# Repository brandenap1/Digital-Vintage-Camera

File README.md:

# Digital-Vintage-Camera
Arduino-controlled image sensor array housed in an analog Conley Kewpie No. 2A analog camera

Mechanical Housing: 3D printed enclosure to house PCBs in camera
Image Sensor PCB: 16 x 16 phototransistor array with MUX control
Controller PCB: MCU with ADC for image data processing 

Future Versions: More optical sensors for higher resolution, Better ADC with RAM for instant image capture, and electronics to automatically move aperture dial

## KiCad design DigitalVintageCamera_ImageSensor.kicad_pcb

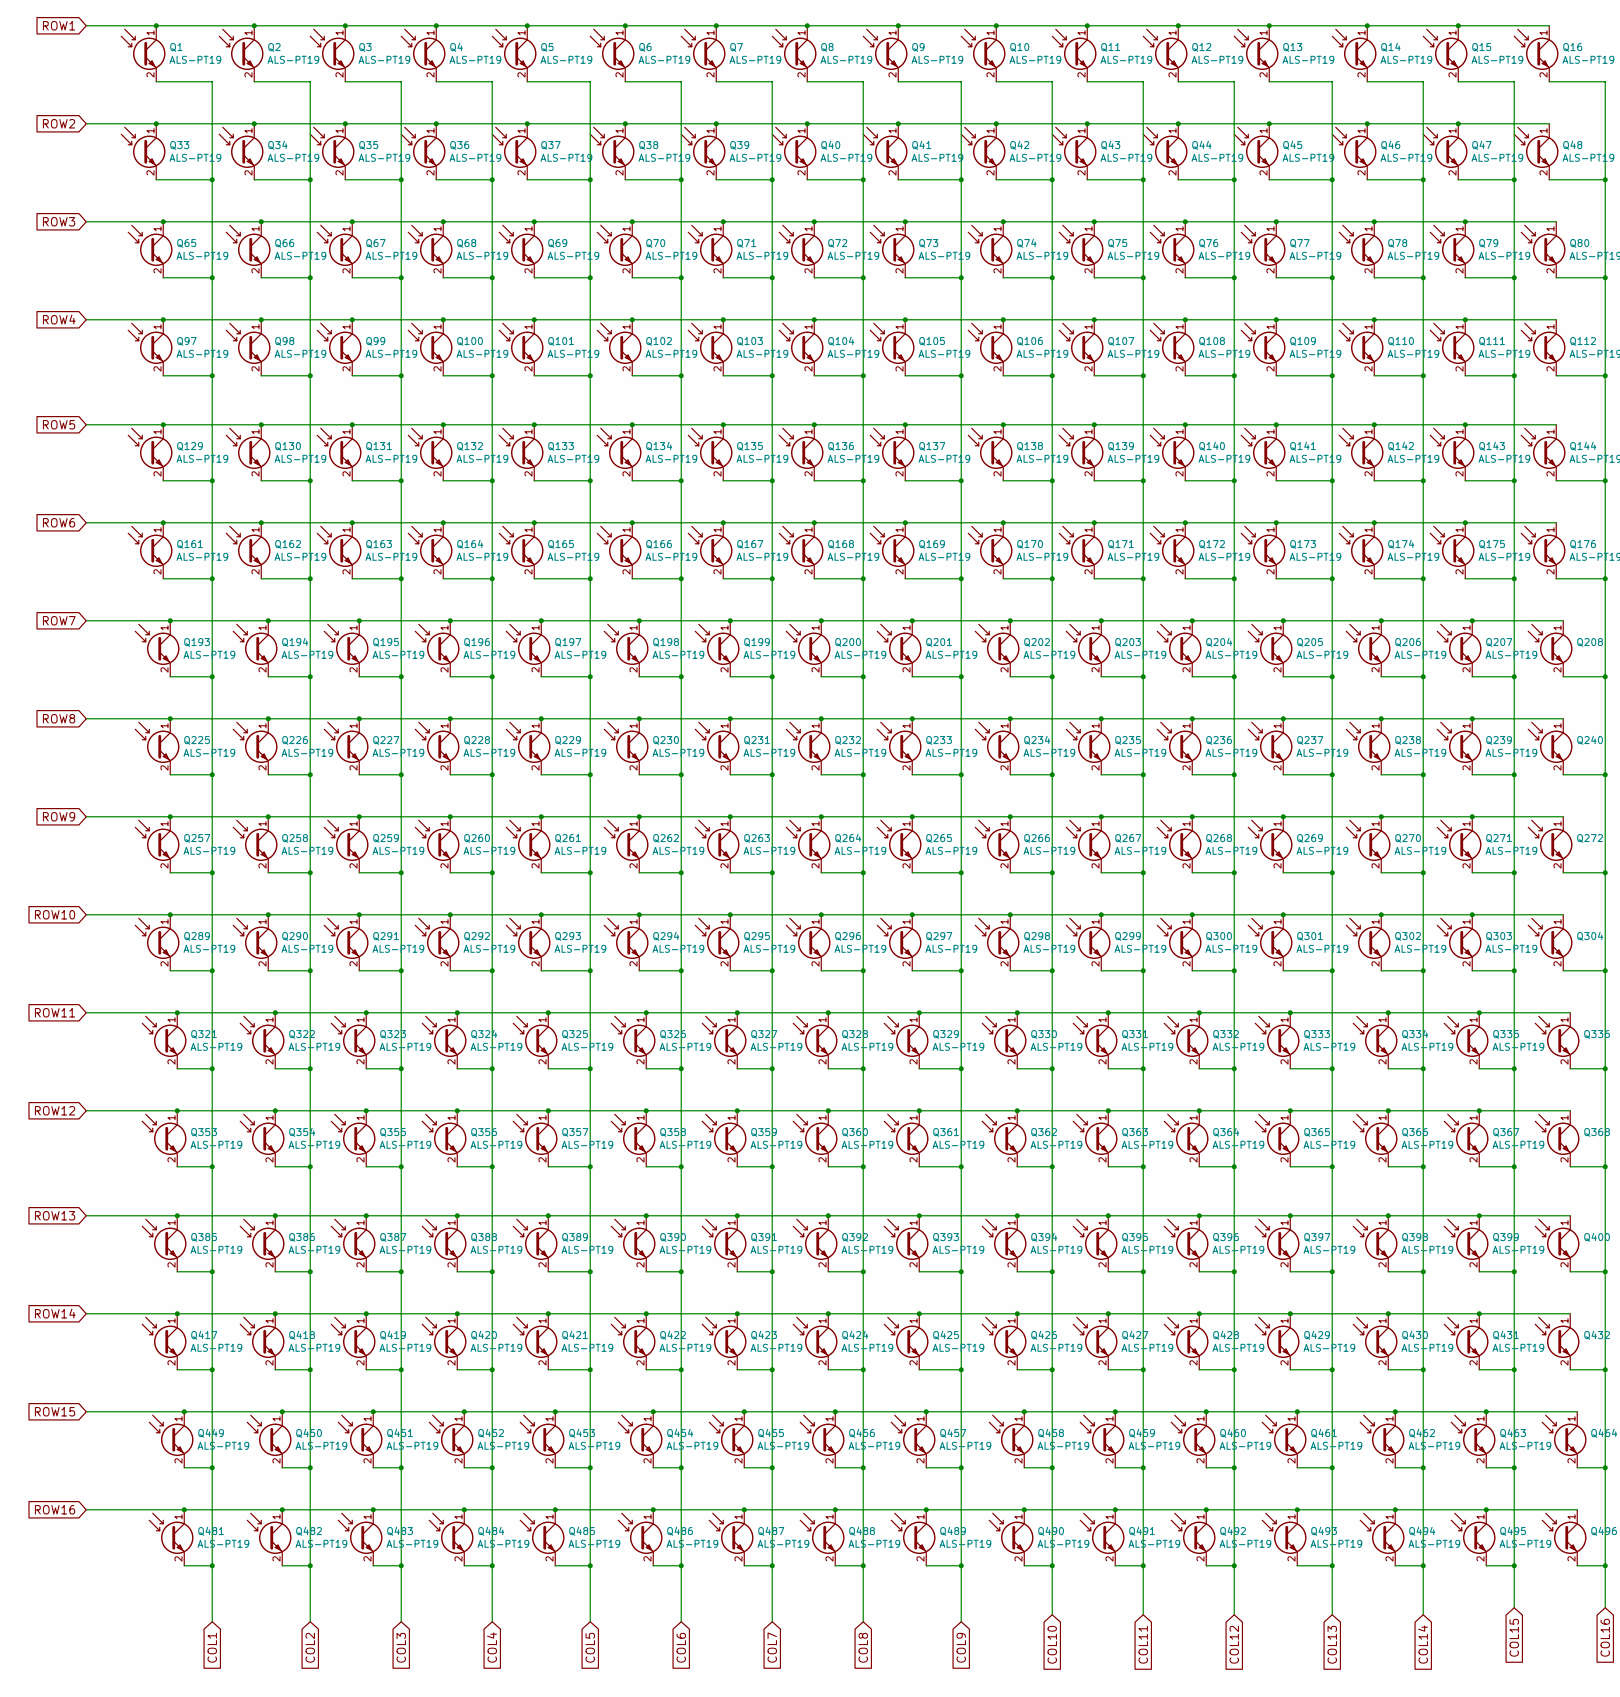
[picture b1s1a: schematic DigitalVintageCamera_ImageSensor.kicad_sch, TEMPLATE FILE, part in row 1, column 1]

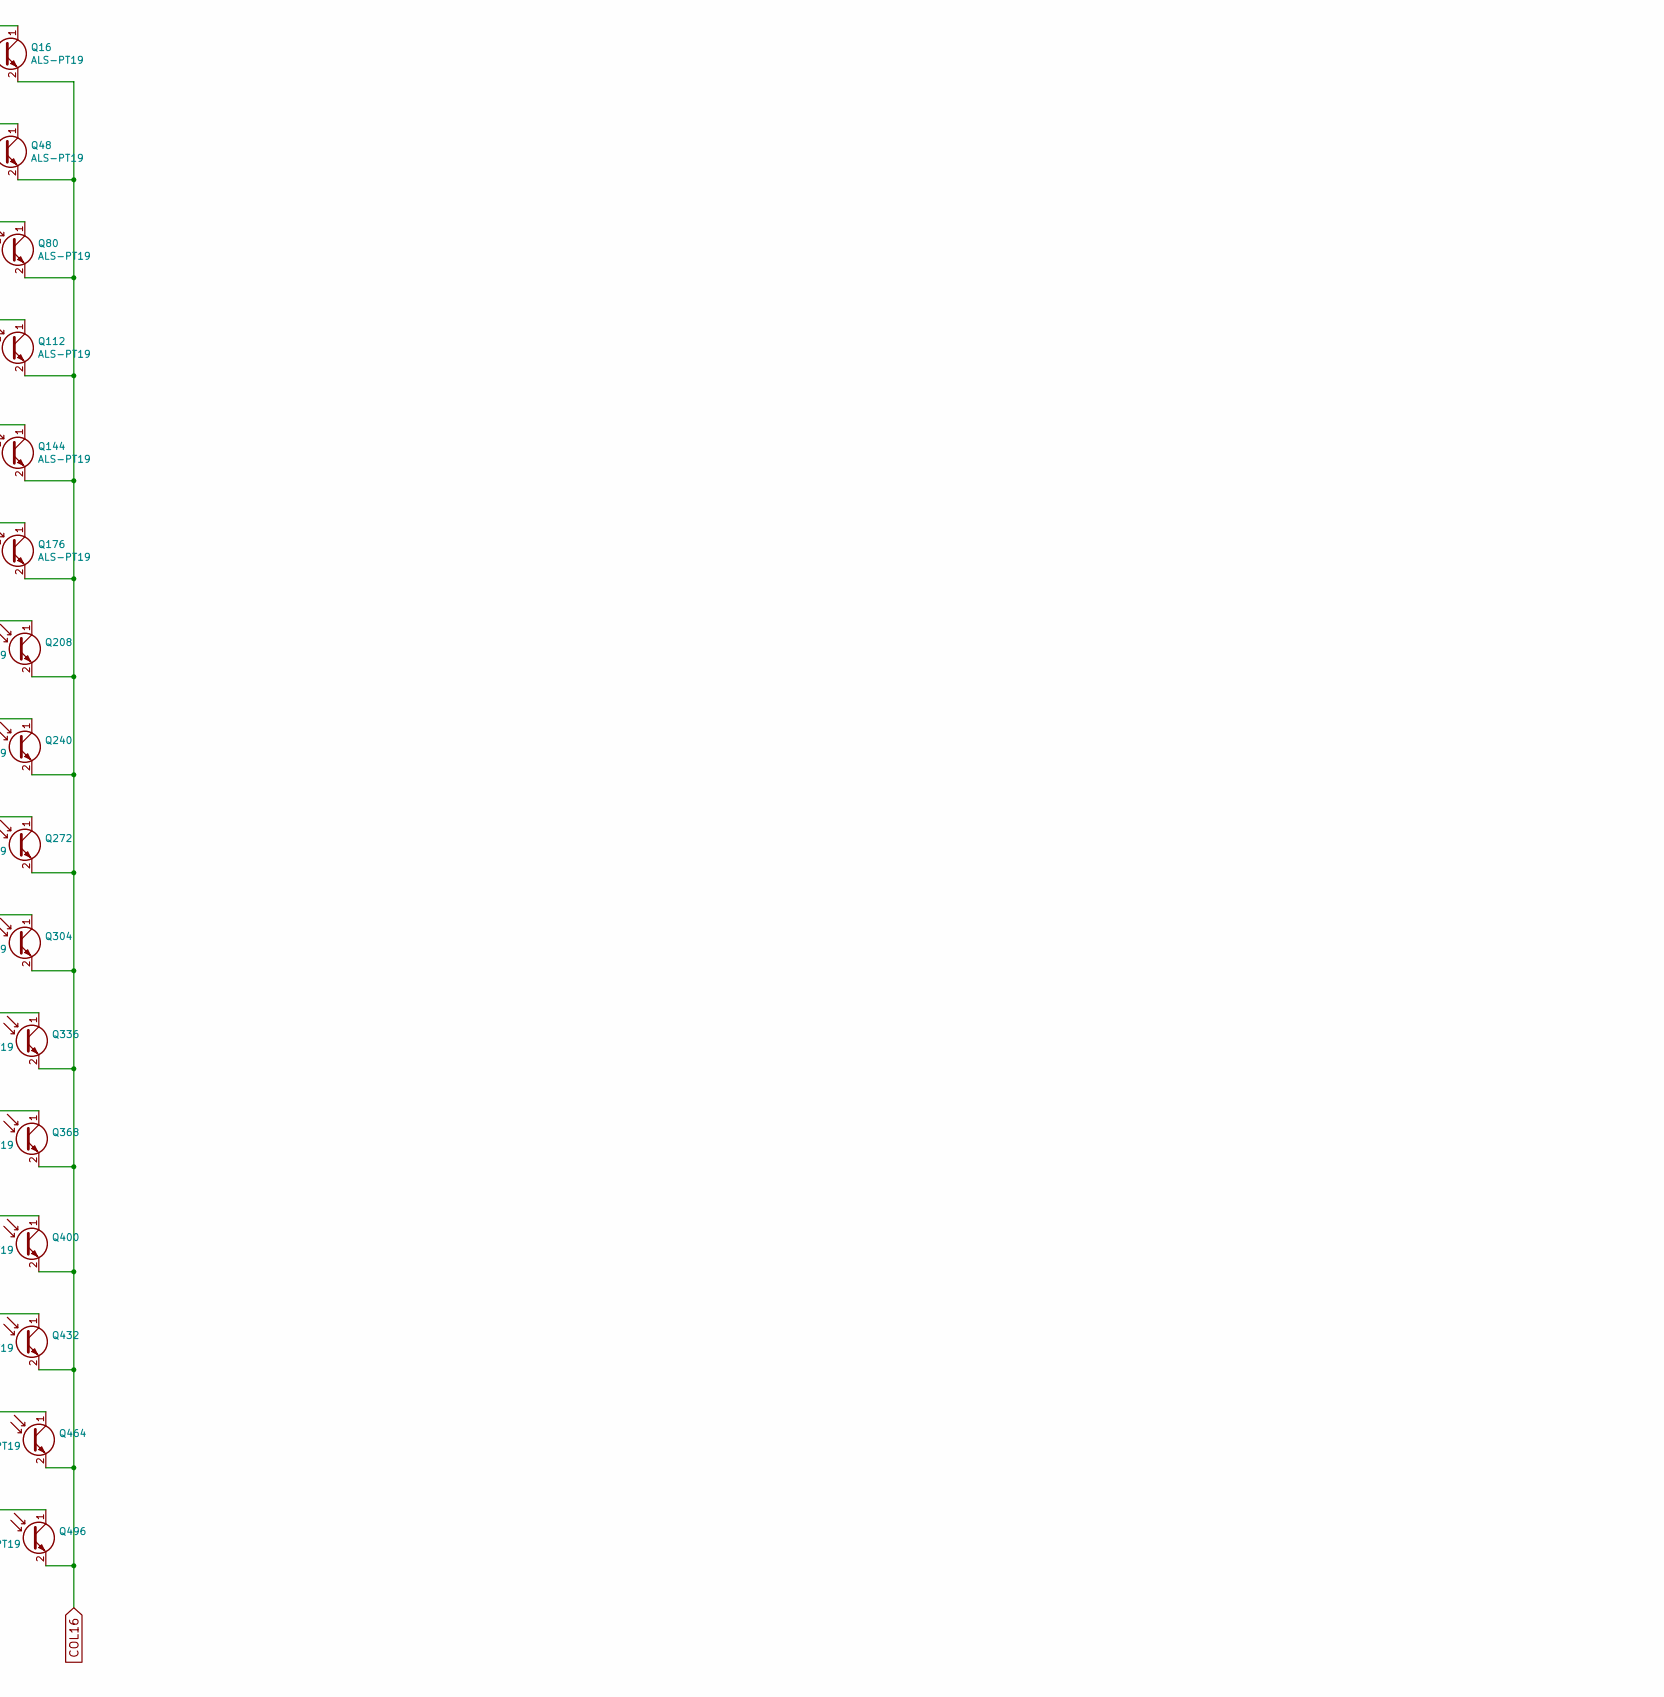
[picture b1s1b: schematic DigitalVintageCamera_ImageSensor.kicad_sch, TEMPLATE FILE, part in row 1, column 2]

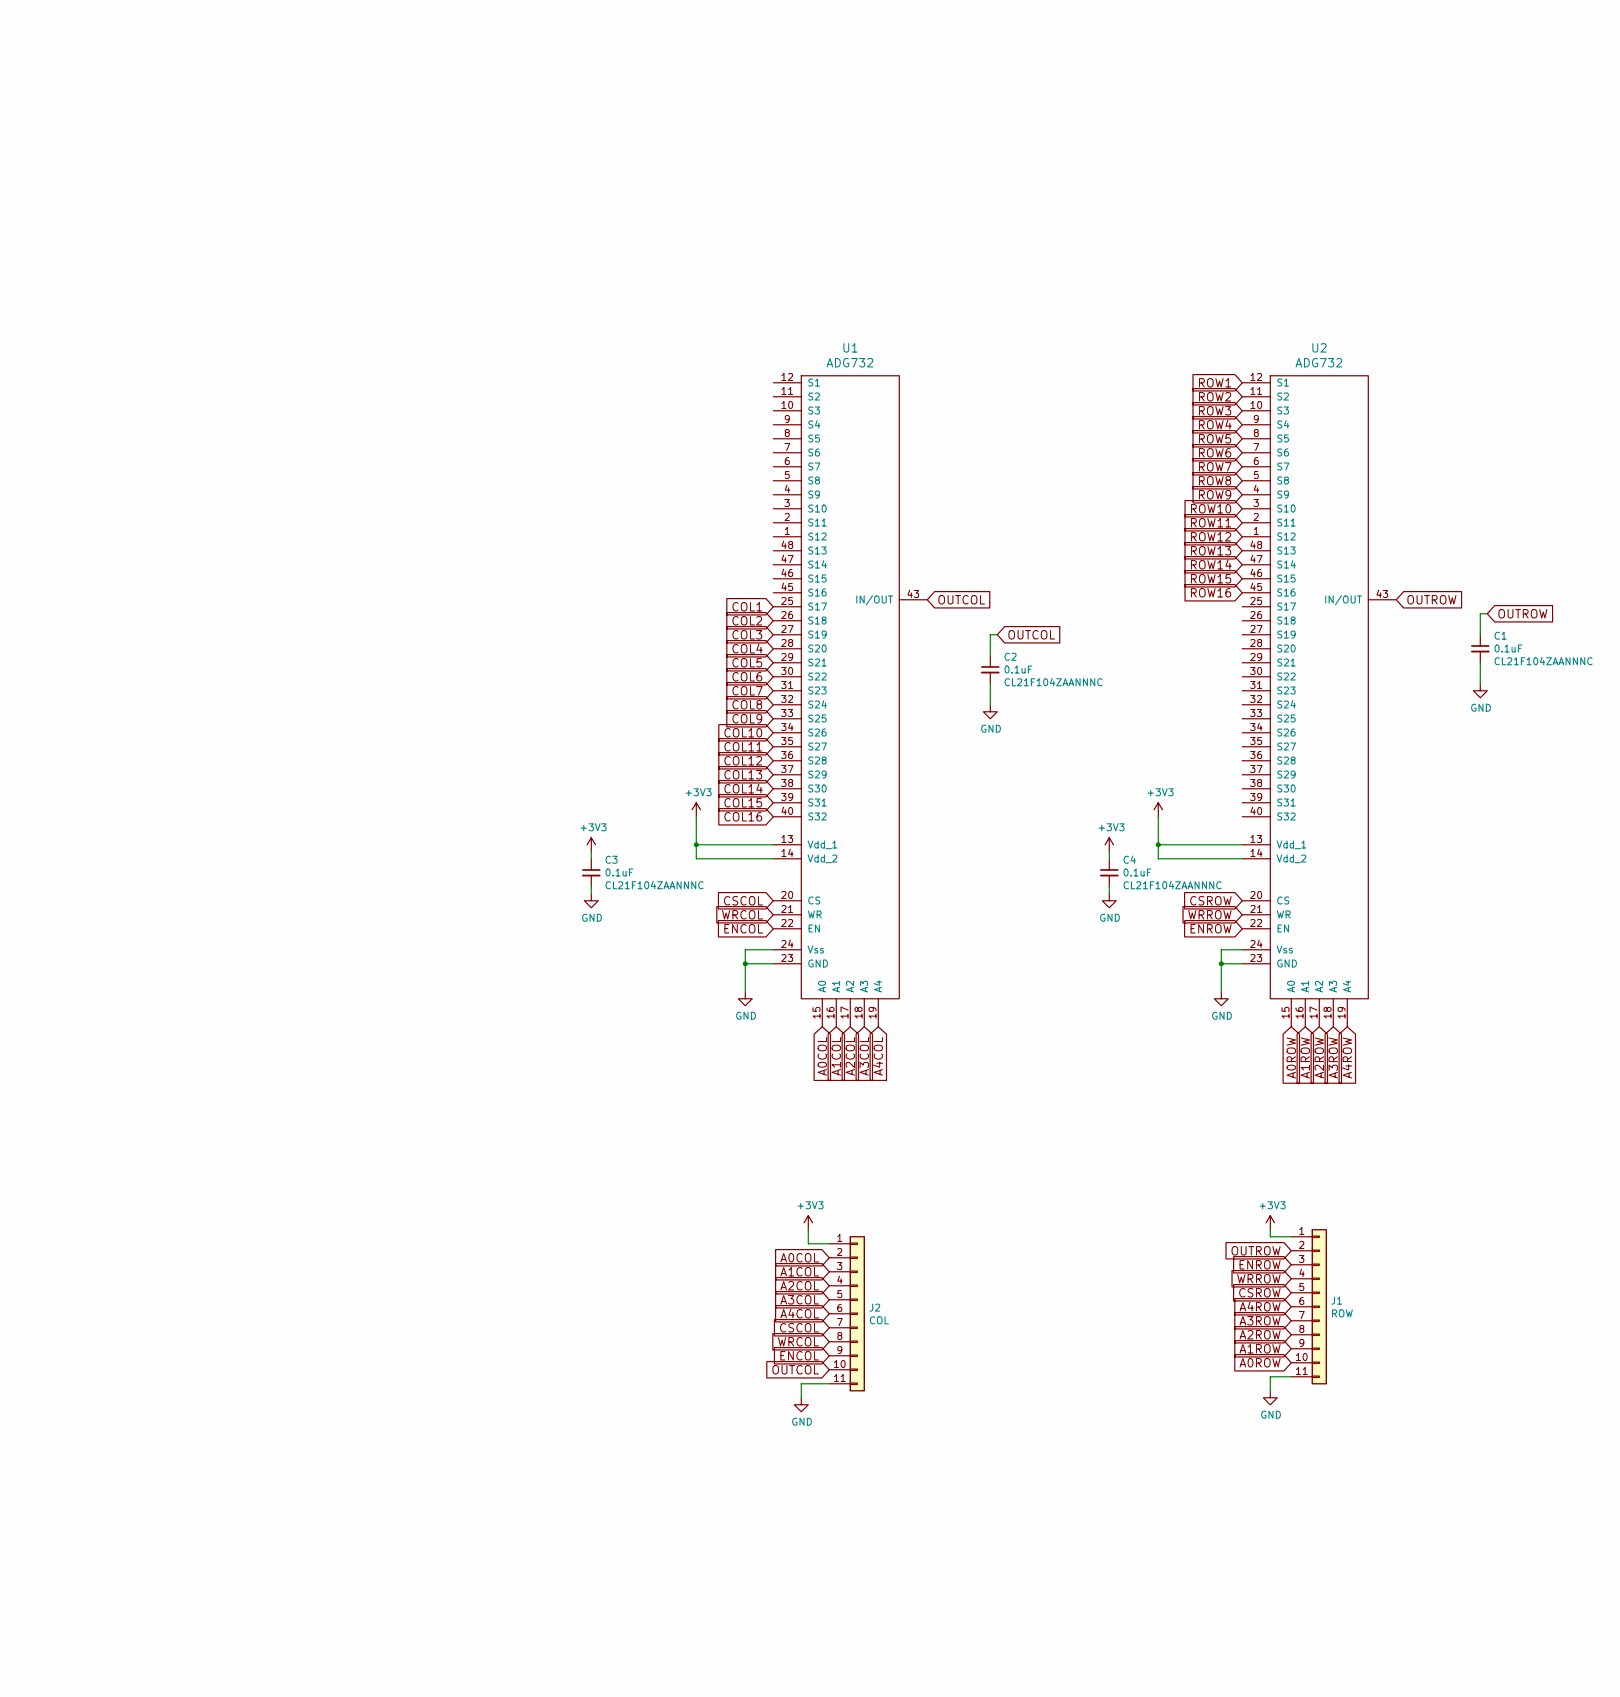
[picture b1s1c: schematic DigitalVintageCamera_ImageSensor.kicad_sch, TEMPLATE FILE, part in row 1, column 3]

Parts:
C1, C2, C3, C4: 0.1uF; C_0805_2012Metric; Digikey Part No. CL21F104ZAANNNC
J1: ROW; PinHeader_1x11_P2.54mm_Vertical; Digikey Part No. 609-5133-ND
J2: COL; PinHeader_1x11_P2.54mm_Vertical; Digikey Part No. 609-5133-ND
Q1, Q2, Q3, Q4, Q5, Q6, Q7, Q8, Q9, Q10, Q11, Q12, Q13, Q14, Q15, Q16, Q33, Q34, Q35, Q36, Q37, Q38, Q39, Q40, Q41, Q42, Q43, Q44, Q45, Q46, Q47, Q48, Q65, Q66, Q67, Q68, Q69, Q70, Q71, Q72, Q73, Q74, Q75, Q76, Q77, Q78, Q79, Q80, Q97, Q98, Q99, Q100, Q101, Q102, Q103, Q104, Q105, Q106, Q107, Q108, Q109, Q110, Q111, Q112, Q129, Q130, Q131, Q132, Q133, Q134, Q135, Q136, Q137, Q138, Q139, Q140, Q141, Q142, Q143, Q144, Q161, Q162, Q163, Q164, Q165, Q166, Q167, Q168, Q169, Q170, Q171, Q172, Q173, Q174, Q175, Q176, Q193, Q194, Q195, Q196, Q197, Q198, Q199, Q200, Q201, Q202, Q203, Q204, Q205, Q206, Q207, Q208, Q225, Q226, Q227, Q228, Q229, Q230, Q231, Q232, Q233, Q234, Q235, Q236, Q237, Q238, Q239, Q240, Q257, Q258, Q259, Q260, Q261, Q262, Q263, Q264, Q265, Q266, Q267, Q268, Q269, Q270, Q271, Q272, Q289, Q290, Q291, Q292, Q293, Q294, Q295, Q296, Q297, Q298, Q299, Q300, Q301, Q302, Q303, Q304, Q321, Q322, Q323, Q324, Q325, Q326, Q327, Q328, Q329, Q330, Q331, Q332, Q333, Q334, Q335, Q336, Q353, Q354, Q355, Q356, Q357, Q358, Q359, Q360, Q361, Q362, Q363, Q364, Q365, Q366, Q367, Q368, Q385, Q386, Q387, Q388, Q389, Q390, Q391, Q392, Q393, Q394, Q395, Q396, Q397, Q398, Q399, Q400, Q417, Q418, Q419, Q420, Q421, Q422, Q423, Q424, Q425, Q426, Q427, Q428, Q429, Q430, Q431, Q432, Q449, Q450, Q451, Q452, Q453, Q454, Q455, Q456, Q457, Q458, Q459, Q460, Q461, Q462, Q463, Q464, Q481, Q482, Q483, Q484, Q485, Q486, Q487, Q488, Q489, Q490, Q491, Q492, Q493, Q494, Q495, Q496: ALS-PT19; Digikey Part No. 1080-1244-1-ND
U1, U2: ADG732; TQFP-48_7x7mm_P0.5mm; Digikey Part No. ADG732BSUZ-REELCT-ND

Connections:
+3V3: C3.1, C4.1, J1.1, J2.1, U1.13 (Vdd_1), U1.14 (Vdd_2), U2.13 (Vdd_1), U2.14 (Vdd_2)
A0COL: J2.2, U1.15 (A0)
A0ROW: J1.10, U2.15 (A0)
A1COL: J2.3, U1.16 (A1)
A1ROW: J1.9, U2.16 (A1)
A2COL: J2.4, U1.17 (A2)
A2ROW: J1.8, U2.17 (A2)
A3COL: J2.5, U1.18 (A3)
A3ROW: J1.7, U2.18 (A3)
A4COL: J2.6, U1.19 (A4)
A4ROW: J1.6, U2.19 (A4)
COL1: Q1.2 (E), Q33.2 (E), Q65.2 (E), Q97.2 (E), Q129.2 (E), Q161.2 (E), Q193.2 (E), Q225.2 (E), Q257.2 (E), Q289.2 (E), Q321.2 (E), Q353.2 (E), Q385.2 (E), Q417.2 (E), Q449.2 (E), Q481.2 (E), U1.25 (S17)
COL2: Q2.2 (E), Q34.2 (E), Q66.2 (E), Q98.2 (E), Q130.2 (E), Q162.2 (E), Q194.2 (E), Q226.2 (E), Q258.2 (E), Q290.2 (E), Q322.2 (E), Q354.2 (E), Q386.2 (E), Q418.2 (E), Q450.2 (E), Q482.2 (E), U1.26 (S18)
COL3: Q3.2 (E), Q35.2 (E), Q67.2 (E), Q99.2 (E), Q131.2 (E), Q163.2 (E), Q195.2 (E), Q227.2 (E), Q259.2 (E), Q291.2 (E), Q323.2 (E), Q355.2 (E), Q387.2 (E), Q419.2 (E), Q451.2 (E), Q483.2 (E), U1.27 (S19)
COL4: Q4.2 (E), Q36.2 (E), Q68.2 (E), Q100.2 (E), Q132.2 (E), Q164.2 (E), Q196.2 (E), Q228.2 (E), Q260.2 (E), Q292.2 (E), Q324.2 (E), Q356.2 (E), Q388.2 (E), Q420.2 (E), Q452.2 (E), Q484.2 (E), U1.28 (S20)
COL5: Q5.2 (E), Q37.2 (E), Q69.2 (E), Q101.2 (E), Q133.2 (E), Q165.2 (E), Q197.2 (E), Q229.2 (E), Q261.2 (E), Q293.2 (E), Q325.2 (E), Q357.2 (E), Q389.2 (E), Q421.2 (E), Q453.2 (E), Q485.2 (E), U1.29 (S21)
COL6: Q6.2 (E), Q38.2 (E), Q70.2 (E), Q102.2 (E), Q134.2 (E), Q166.2 (E), Q198.2 (E), Q230.2 (E), Q262.2 (E), Q294.2 (E), Q326.2 (E), Q358.2 (E), Q390.2 (E), Q422.2 (E), Q454.2 (E), Q486.2 (E), U1.30 (S22)
COL7: Q7.2 (E), Q39.2 (E), Q71.2 (E), Q103.2 (E), Q135.2 (E), Q167.2 (E), Q199.2 (E), Q231.2 (E), Q263.2 (E), Q295.2 (E), Q327.2 (E), Q359.2 (E), Q391.2 (E), Q423.2 (E), Q455.2 (E), Q487.2 (E), U1.31 (S23)
COL8: Q8.2 (E), Q40.2 (E), Q72.2 (E), Q104.2 (E), Q136.2 (E), Q168.2 (E), Q200.2 (E), Q232.2 (E), Q264.2 (E), Q296.2 (E), Q328.2 (E), Q360.2 (E), Q392.2 (E), Q424.2 (E), Q456.2 (E), Q488.2 (E), U1.32 (S24)
COL9: Q9.2 (E), Q41.2 (E), Q73.2 (E), Q105.2 (E), Q137.2 (E), Q169.2 (E), Q201.2 (E), Q233.2 (E), Q265.2 (E), Q297.2 (E), Q329.2 (E), Q361.2 (E), Q393.2 (E), Q425.2 (E), Q457.2 (E), Q489.2 (E), U1.33 (S25)
COL10: Q10.2 (E), Q42.2 (E), Q74.2 (E), Q106.2 (E), Q138.2 (E), Q170.2 (E), Q202.2 (E), Q234.2 (E), Q266.2 (E), Q298.2 (E), Q330.2 (E), Q362.2 (E), Q394.2 (E), Q426.2 (E), Q458.2 (E), Q490.2 (E), U1.34 (S26)
COL11: Q11.2 (E), Q43.2 (E), Q75.2 (E), Q107.2 (E), Q139.2 (E), Q171.2 (E), Q203.2 (E), Q235.2 (E), Q267.2 (E), Q299.2 (E), Q331.2 (E), Q363.2 (E), Q395.2 (E), Q427.2 (E), Q459.2 (E), Q491.2 (E), U1.35 (S27)
COL12: Q12.2 (E), Q44.2 (E), Q76.2 (E), Q108.2 (E), Q140.2 (E), Q172.2 (E), Q204.2 (E), Q236.2 (E), Q268.2 (E), Q300.2 (E), Q332.2 (E), Q364.2 (E), Q396.2 (E), Q428.2 (E), Q460.2 (E), Q492.2 (E), U1.36 (S28)
COL13: Q13.2 (E), Q45.2 (E), Q77.2 (E), Q109.2 (E), Q141.2 (E), Q173.2 (E), Q205.2 (E), Q237.2 (E), Q269.2 (E), Q301.2 (E), Q333.2 (E), Q365.2 (E), Q397.2 (E), Q429.2 (E), Q461.2 (E), Q493.2 (E), U1.37 (S29)
COL14: Q14.2 (E), Q46.2 (E), Q78.2 (E), Q110.2 (E), Q142.2 (E), Q174.2 (E), Q206.2 (E), Q238.2 (E), Q270.2 (E), Q302.2 (E), Q334.2 (E), Q366.2 (E), Q398.2 (E), Q430.2 (E), Q462.2 (E), Q494.2 (E), U1.38 (S30)
COL15: Q15.2 (E), Q47.2 (E), Q79.2 (E), Q111.2 (E), Q143.2 (E), Q175.2 (E), Q207.2 (E), Q239.2 (E), Q271.2 (E), Q303.2 (E), Q335.2 (E), Q367.2 (E), Q399.2 (E), Q431.2 (E), Q463.2 (E), Q495.2 (E), U1.39 (S31)
COL16: Q16.2 (E), Q48.2 (E), Q80.2 (E), Q112.2 (E), Q144.2 (E), Q176.2 (E), Q208.2 (E), Q240.2 (E), Q272.2 (E), Q304.2 (E), Q336.2 (E), Q368.2 (E), Q400.2 (E), Q432.2 (E), Q464.2 (E), Q496.2 (E), U1.40 (S32)
CSCOL: J2.7, U1.20 (CS)
CSROW: J1.5, U2.20 (CS)
ENCOL: J2.9, U1.22 (EN)
ENROW: J1.3, U2.22 (EN)
GND: C1.2, C2.2, C3.2, C4.2, J1.11, J2.11, U1.23 (GND), U1.24 (Vss), U2.23 (GND), U2.24 (Vss)
OUTCOL: C2.1, J2.10, U1.43 (IN/OUT)
OUTROW: C1.1, J1.2, U2.43 (IN/OUT)
ROW1: Q1.1 (C), Q2.1 (C), Q3.1 (C), Q4.1 (C), Q5.1 (C), Q6.1 (C), Q7.1 (C), Q8.1 (C), Q9.1 (C), Q10.1 (C), Q11.1 (C), Q12.1 (C), Q13.1 (C), Q14.1 (C), Q15.1 (C), Q16.1 (C), U2.12 (S1)
ROW2: Q33.1 (C), Q34.1 (C), Q35.1 (C), Q36.1 (C), Q37.1 (C), Q38.1 (C), Q39.1 (C), Q40.1 (C), Q41.1 (C), Q42.1 (C), Q43.1 (C), Q44.1 (C), Q45.1 (C), Q46.1 (C), Q47.1 (C), Q48.1 (C), U2.11 (S2)
ROW3: Q65.1 (C), Q66.1 (C), Q67.1 (C), Q68.1 (C), Q69.1 (C), Q70.1 (C), Q71.1 (C), Q72.1 (C), Q73.1 (C), Q74.1 (C), Q75.1 (C), Q76.1 (C), Q77.1 (C), Q78.1 (C), Q79.1 (C), Q80.1 (C), U2.10 (S3)
ROW4: Q97.1 (C), Q98.1 (C), Q99.1 (C), Q100.1 (C), Q101.1 (C), Q102.1 (C), Q103.1 (C), Q104.1 (C), Q105.1 (C), Q106.1 (C), Q107.1 (C), Q108.1 (C), Q109.1 (C), Q110.1 (C), Q111.1 (C), Q112.1 (C), U2.9 (S4)
ROW5: Q129.1 (C), Q130.1 (C), Q131.1 (C), Q132.1 (C), Q133.1 (C), Q134.1 (C), Q135.1 (C), Q136.1 (C), Q137.1 (C), Q138.1 (C), Q139.1 (C), Q140.1 (C), Q141.1 (C), Q142.1 (C), Q143.1 (C), Q144.1 (C), U2.8 (S5)
ROW6: Q161.1 (C), Q162.1 (C), Q163.1 (C), Q164.1 (C), Q165.1 (C), Q166.1 (C), Q167.1 (C), Q168.1 (C), Q169.1 (C), Q170.1 (C), Q171.1 (C), Q172.1 (C), Q173.1 (C), Q174.1 (C), Q175.1 (C), Q176.1 (C), U2.7 (S6)
ROW7: Q193.1 (C), Q194.1 (C), Q195.1 (C), Q196.1 (C), Q197.1 (C), Q198.1 (C), Q199.1 (C), Q200.1 (C), Q201.1 (C), Q202.1 (C), Q203.1 (C), Q204.1 (C), Q205.1 (C), Q206.1 (C), Q207.1 (C), Q208.1 (C), U2.6 (S7)
ROW8: Q225.1 (C), Q226.1 (C), Q227.1 (C), Q228.1 (C), Q229.1 (C), Q230.1 (C), Q231.1 (C), Q232.1 (C), Q233.1 (C), Q234.1 (C), Q235.1 (C), Q236.1 (C), Q237.1 (C), Q238.1 (C), Q239.1 (C), Q240.1 (C), U2.5 (S8)
ROW9: Q257.1 (C), Q258.1 (C), Q259.1 (C), Q260.1 (C), Q261.1 (C), Q262.1 (C), Q263.1 (C), Q264.1 (C), Q265.1 (C), Q266.1 (C), Q267.1 (C), Q268.1 (C), Q269.1 (C), Q270.1 (C), Q271.1 (C), Q272.1 (C), U2.4 (S9)
ROW10: Q289.1 (C), Q290.1 (C), Q291.1 (C), Q292.1 (C), Q293.1 (C), Q294.1 (C), Q295.1 (C), Q296.1 (C), Q297.1 (C), Q298.1 (C), Q299.1 (C), Q300.1 (C), Q301.1 (C), Q302.1 (C), Q303.1 (C), Q304.1 (C), U2.3 (S10)
ROW11: Q321.1 (C), Q322.1 (C), Q323.1 (C), Q324.1 (C), Q325.1 (C), Q326.1 (C), Q327.1 (C), Q328.1 (C), Q329.1 (C), Q330.1 (C), Q331.1 (C), Q332.1 (C), Q333.1 (C), Q334.1 (C), Q335.1 (C), Q336.1 (C), U2.2 (S11)
ROW12: Q353.1 (C), Q354.1 (C), Q355.1 (C), Q356.1 (C), Q357.1 (C), Q358.1 (C), Q359.1 (C), Q360.1 (C), Q361.1 (C), Q362.1 (C), Q363.1 (C), Q364.1 (C), Q365.1 (C), Q366.1 (C), Q367.1 (C), Q368.1 (C), U2.1 (S12)
ROW13: Q385.1 (C), Q386.1 (C), Q387.1 (C), Q388.1 (C), Q389.1 (C), Q390.1 (C), Q391.1 (C), Q392.1 (C), Q393.1 (C), Q394.1 (C), Q395.1 (C), Q396.1 (C), Q397.1 (C), Q398.1 (C), Q399.1 (C), Q400.1 (C), U2.48 (S13)
ROW14: Q417.1 (C), Q418.1 (C), Q419.1 (C), Q420.1 (C), Q421.1 (C), Q422.1 (C), Q423.1 (C), Q424.1 (C), Q425.1 (C), Q426.1 (C), Q427.1 (C), Q428.1 (C), Q429.1 (C), Q430.1 (C), Q431.1 (C), Q432.1 (C), U2.47 (S14)
ROW15: Q449.1 (C), Q450.1 (C), Q451.1 (C), Q452.1 (C), Q453.1 (C), Q454.1 (C), Q455.1 (C), Q456.1 (C), Q457.1 (C), Q458.1 (C), Q459.1 (C), Q460.1 (C), Q461.1 (C), Q462.1 (C), Q463.1 (C), Q464.1 (C), U2.46 (S15)
ROW16: Q481.1 (C), Q482.1 (C), Q483.1 (C), Q484.1 (C), Q485.1 (C), Q486.1 (C), Q487.1 (C), Q488.1 (C), Q489.1 (C), Q490.1 (C), Q491.1 (C), Q492.1 (C), Q493.1 (C), Q494.1 (C), Q495.1 (C), Q496.1 (C), U2.45 (S16)
WRCOL: J2.8, U1.21 (WR)
WRROW: J1.4, U2.21 (WR)

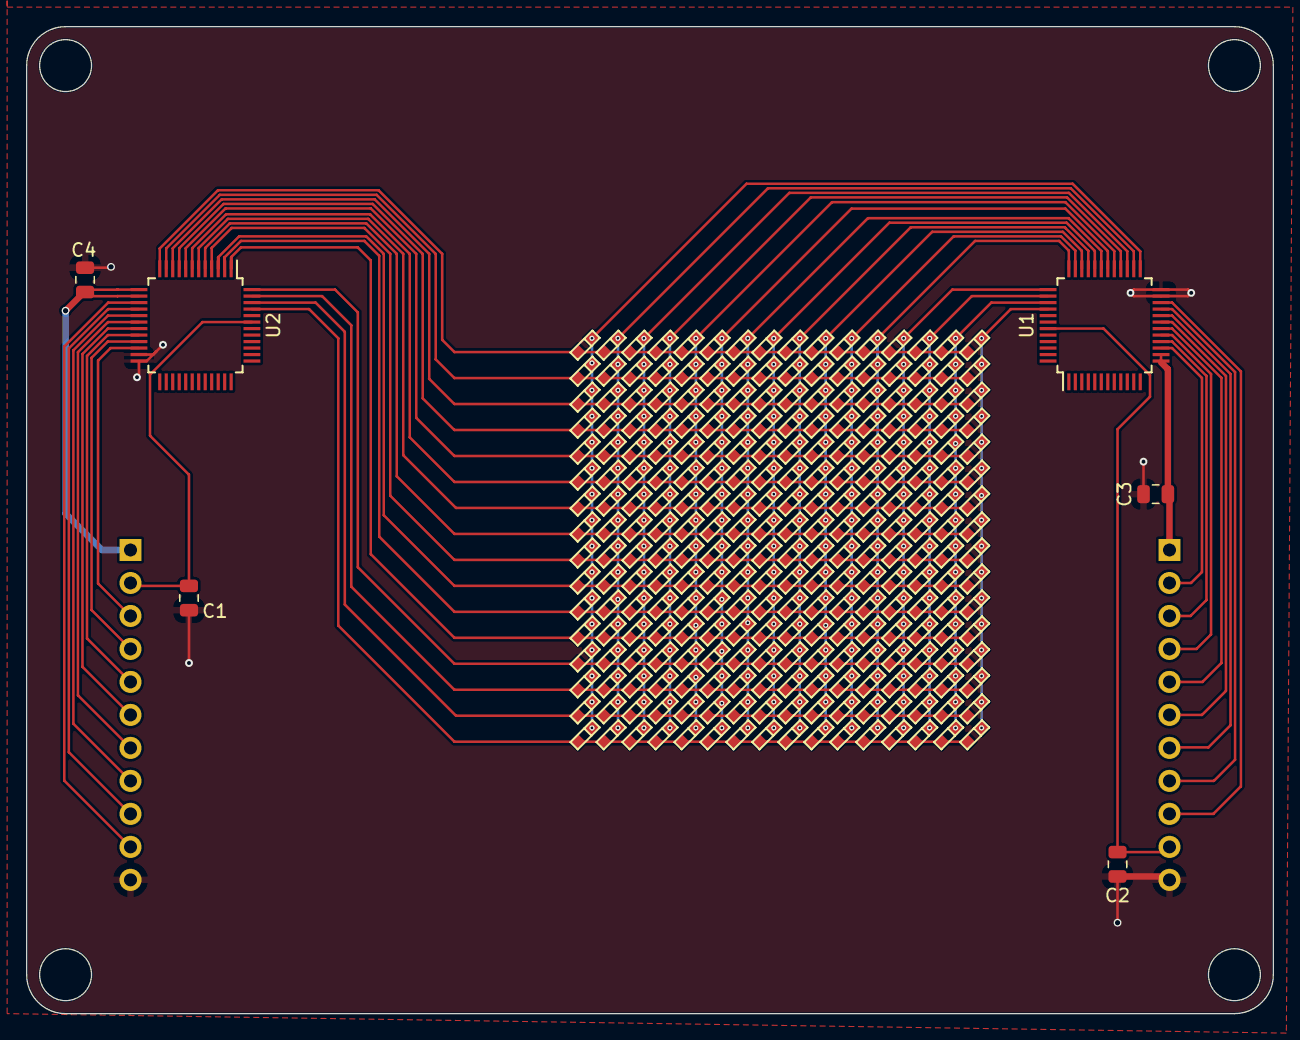
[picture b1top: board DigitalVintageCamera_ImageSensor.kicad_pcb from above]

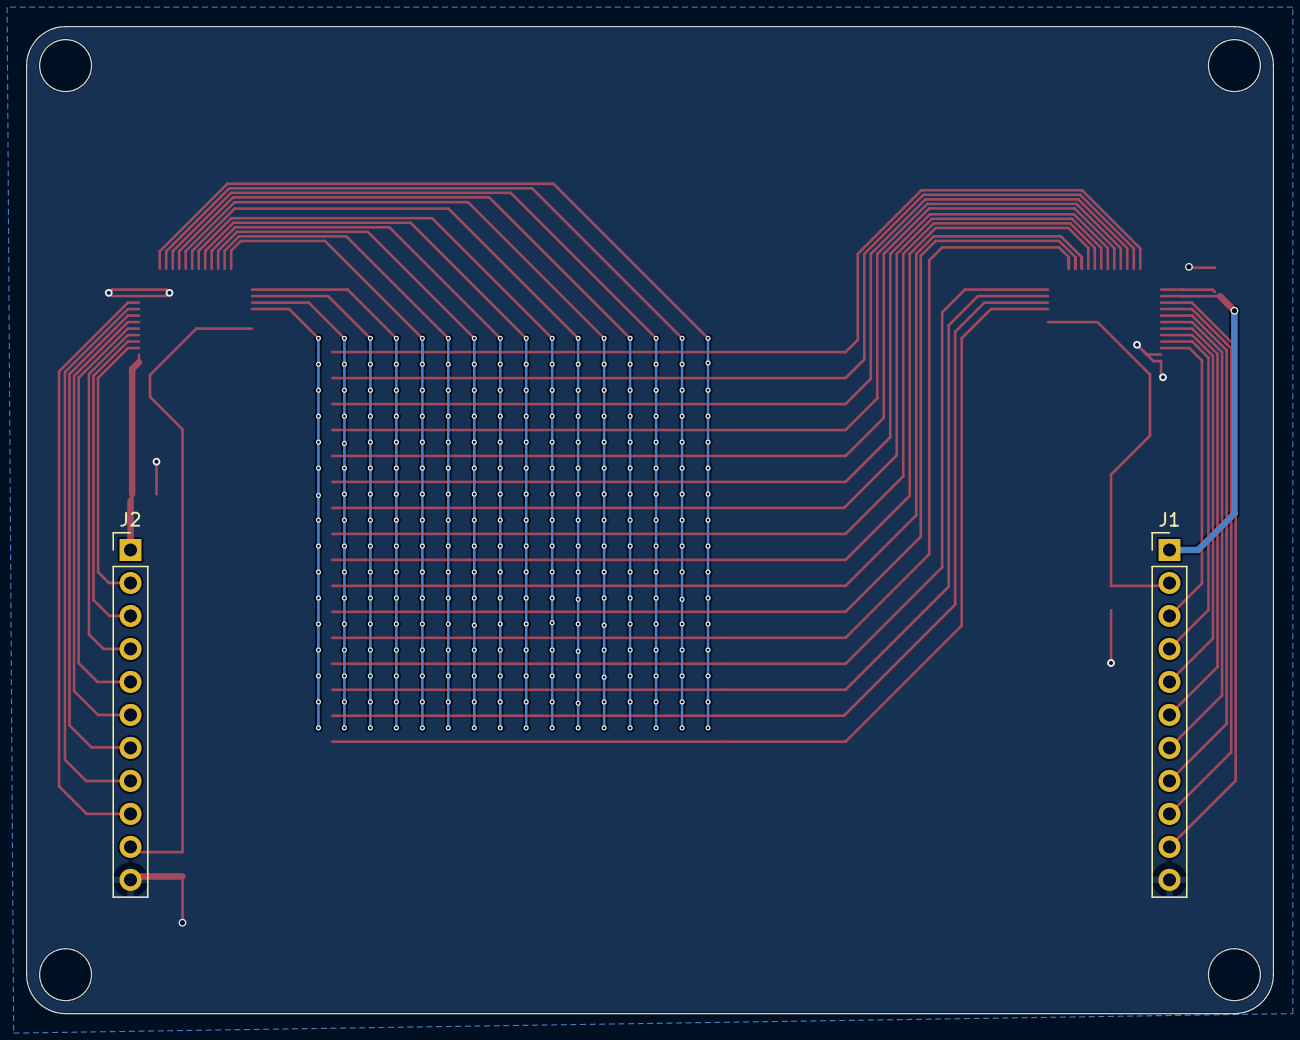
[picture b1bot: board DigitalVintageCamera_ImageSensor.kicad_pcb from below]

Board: 2 copper layers, 96.0 x 76.0 mm, 264 parts (2 on the bottom side), 52 nets.
